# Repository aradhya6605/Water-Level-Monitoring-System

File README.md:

# Water-Level-Monitoring-System
Smart IoT-based Water Level Monitoring System using ESP32, ultrasonic sensor, and real-time alerts for tank water management

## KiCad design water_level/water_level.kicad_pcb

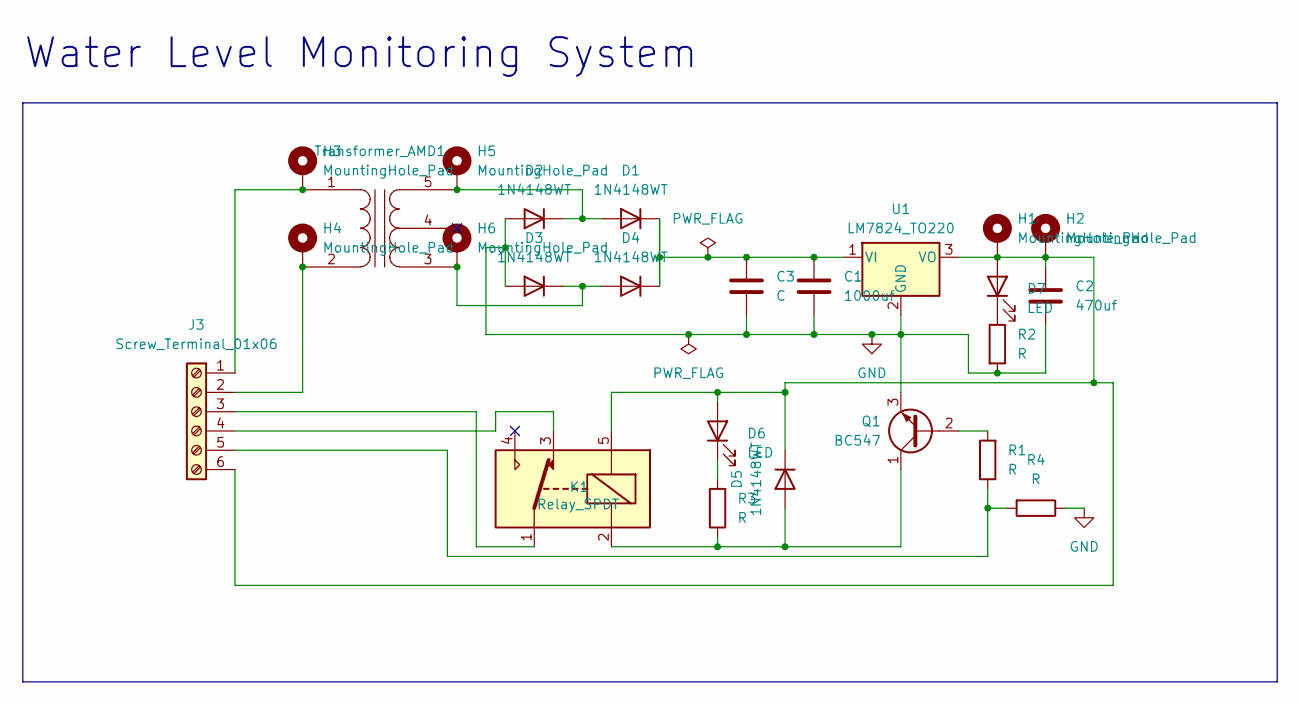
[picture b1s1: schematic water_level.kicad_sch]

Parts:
C1: 1000uf; C_Radial_D10.0mm_H12.5mm_P5.00mm
C2: 470uf; C_Radial_D10.0mm_H12.5mm_P5.00mm
C3: C; C_Disc_D7.5mm_W5.0mm_P5.00mm
D1, D2, D3, D4, D5: 1N4148WT; D_A-405_P10.16mm_Horizontal
D6, D7: LED; LED_D3.0mm
H1, H2, H3, H4, H5, H6: MountingHole_Pad; MountingHole_2.2mm_M2_DIN965_Pad
J3: Screw_Terminal_01x06; TerminalBlock_Phoenix_PT-1,5-6-5.0-H_1x06_P5.00mm_Horizontal
K1: Relay_SPDT; Relay_SPDT_SANYOU_SRD_Series_Form_C
Q1: BC547; TO-92_HandSolder
R1, R2, R3, R4: R; R_Axial_DIN0207_L6.3mm_D2.5mm_P10.16mm_Horizontal
Transformer_AMD1: Transfromer
U1: LM7824_TO220; TO-220-3_Vertical

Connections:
GND: C1.2, C2.2, C3.2, D2.2 (A), D3.2 (A), Q1.3 (E), R2.2, R4.1, U1.2 (GND)
unnamed: D1.2 (A), D2.1 (K), H5.1, Transformer_AMD1.5
unnamed: C1.1, C3.1, D1.1 (K), D4.1 (K), U1.1 (VI)
unnamed: D3.1 (K), D4.2 (A), H6.1, Transformer_AMD1.3
unnamed: D5.2 (A), K1.2, Q1.1 (C), R3.1
unnamed: C2.1, D5.1 (K), D6.2 (A), D7.2 (A), H1.1, H2.1, J3.6, K1.5, U1.3 (VO)
unnamed: D6.1 (K), R3.2
unnamed: D7.1 (K), R2.1
unnamed: H3.1, J3.1, Transformer_AMD1.1
unnamed: H4.1, J3.2, Transformer_AMD1.2
unnamed: J3.3, K1.1
unnamed: J3.4, K1.3
unnamed: J3.5, R1.1, R4.2
unnamed: Q1.2 (B), R1.2

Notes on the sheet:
Water Level Monitoring System

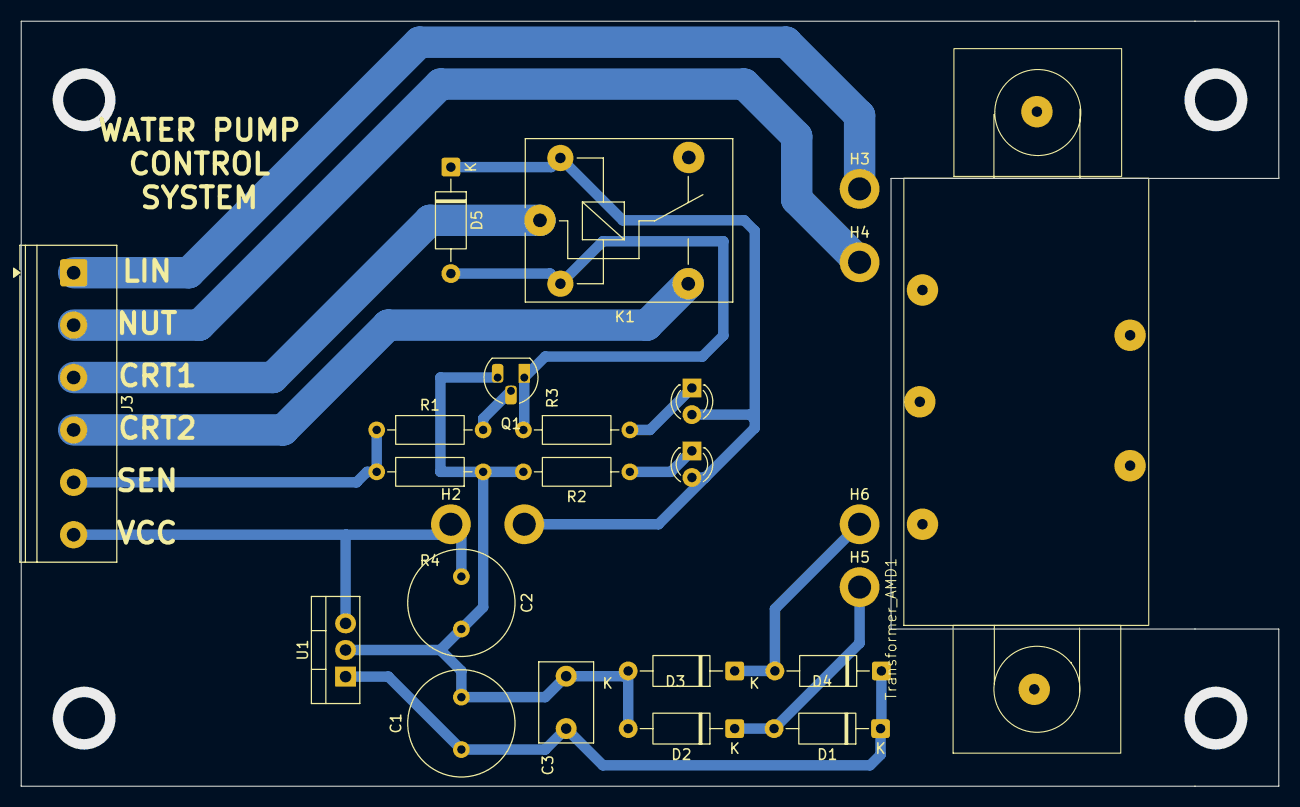
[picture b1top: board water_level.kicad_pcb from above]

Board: 2 copper layers, 120.0 x 73.0 mm, 25 parts (0 on the bottom side), 14 nets.

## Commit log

2026-04-24 Rename lora_receiver/lora_receiver.ino to lora_receiver.ino
2026-04-24 Rename lora_transmitter.ino to .ino
2026-04-24 Rename lora_transmitter/.ino to lora_transmitter.ino
